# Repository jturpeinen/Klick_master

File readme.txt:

**********************************************************
*************  Important Instructions Follow  ************
**********************************************************

All files exported to: Z:\\47\\32\\4732651\\9\Eagle\2016-07-08_01-20-50\2016-07-08_01-20-50.xml

**********************************************************
*****************Schematic Instructions  *******************
**********************************************************

To import your new Schematic file into Eagle:

1. Unzip the downloaded folder files to local directory and Start Eagle.
2. Select "File"->"Open"->"Schematic..." from the menu at the top of
the screen.
3. Browse to your newly exported file and select the ".sch" file extension.
4. You should now see your schamtic available in Eagle.

**********************************************************
*******************  PCB Instructions  *******************
**********************************************************

To import your new BOARD file into Eagle:

1. Unzip the downloaded folder files to local directory and Start Eagle.
2. Select "File"->"Open"->"Board..." from the menu at the top of
the screen.
3. Browse to your newly exported file and select the ".brd" file extension.
4. Planes will need to be repoured to update the polygon fills
	1. Once your board is loaded and before the repour, the default design rule
	   should be updated for Mask and thermal relief.
		a. Goto Edit and select Design Rules.
			-Select Masks Tab; Set Stop (Min & Max) to 0.0mm
			-Select Supply Tab; Set Thermal Isolation to 0.0mm
	2. To pour the polygon fills, goto Tools and select Ratsnest
	3. The polygons should all be filled now.
5. You should now have an image of your board available in Eagle.

**********************************************************
*******************  LIB Instructions  *******************
**********************************************************

To import your new library into Eagle:

1. Start Eagle.
2. Select "File"->"New"->"Library" from the menu.
3. In the blank library window, select "File" -> "Execute Script"
from the menu.
5. Browse to your newly exported Eagle Script file (".scr" file extension)
6. After opening the file, the script will populate the new library.
Layer 93 should NOT exist.
7. Use "File"->"Save" (or "Save As..") to save the library to the desired
location in Eagle native format.

For additional information, please visit this site:
http://www.accelerated-designs.com/help/Eagle_import.html

You may also find this video helpful:
http://youtu.be/5jGuWY-Yy3Q

**********************************************************
**********************************************************
**********************************************************

Padstack "RX78p74Y236p22D0T" renamed to "RX78p74Y236p22D0"
Component "CC0805KRX7R9BB222" renamed to "CC0805KRX7R9BB222"
Component "GRM21BR61E475MA12L" renamed to "GRM21BR61E475MA12L"
Component "GRM31CR71H475KA12L" renamed to "GRM31CR71H475KA12L"
Component "TPS61170DRVR" renamed to "TPS61170DRVR"
Component "SRN6045-220M" renamed to "SRN6045-220M"
Component "CRCW040246K4FKED" renamed to "CRCW040246K4FKED"
Component "CRCW040210K5FKED" renamed to "CRCW040210K5FKED"
Component "CRCW0402226KFKED" renamed to "CRCW0402226KFKED"
Component "TP-1502" renamed to "TP-1502"
Component "PMEG6010CEH,115" renamed to "PMEG6010CEH,115"

Ultra Librarian Gold 8.1.44 Process Report

Message - Padstack "RX44Y57D0T" Shape(4) is a CIRCLE with no diameter.
Message - Padstack "RX44Y71D0T" Shape(4) is a CIRCLE with no diameter.
Message - Padstack "RX78p74Y236p22D0" Shape(4) is a CIRCLE with no diameter.
Message - Padstack "RX22Y24D0T" Shape(4) is a CIRCLE with no diameter.
Message - Padstack "RX24Y14D0T" Shape(4) is a CIRCLE with no diameter.
Message - Padstack "RX39Y63D0T" Shape(4) is a CIRCLE with no diameter.
Message - Padstack "R10470470000202A" Shape(4) is a CIRCLE with no diameter.
Message - Component "CC0805KRX7R9BB222" attribute "Cap" references text style "" that is not in the database.
The default pattern text style "H50s3" was substituted.
Message - Component "CC0805KRX7R9BB222" attribute "ESR" references text style "" that is not in the database.
The default pattern text style "H50s3" was substituted.
Message - Component "CC0805KRX7R9BB222" attribute "IRMS" references text style "" that is not in the database.
The default pattern text style "H50s3" was substituted.
Message - Component "CC0805KRX7R9BB222" attribute "VDC" references text style "" that is not in the database.
The default pattern text style "H50s3" was substituted.
Message - Component "GRM21BR61E475MA12L" attribute "Datasheet URL" references text style "" that is not in the database.
The default pattern text style "H50s3" was substituted.
Message - Component "GRM21BR61E475MA12L" attribute "Cap" references text style "" that is not in the database.
The default pattern text style "H50s3" was substituted.
Message - Component "GRM21BR61E475MA12L" attribute "ESR" references text style "" that is not in the database.
The default pattern text style "H50s3" was substituted.
Message - Component "GRM21BR61E475MA12L" attribute "IRMS" references text style "" that is not in the database.
The default pattern text style "H50s3" was substituted.
Message - Component "GRM21BR61E475MA12L" attribute "VDC" references text style "" that is not in the database.
The default pattern text style "H50s3" was substituted.
Message - Component "GRM31CR71H475KA12L" attribute "Cap" references text style "" that is not in the database.
The default pattern text style "H50s3" was substituted.
Message - Component "GRM31CR71H475KA12L" attribute "ESR" references text style "" that is not in the database.
The default pattern text style "H50s3" was substituted.
Message - Component "GRM31CR71H475KA12L" attribute "IRMS" references text style "" that is not in the database.
The default pattern text style "H50s3" was substituted.
Message - Component "GRM31CR71H475KA12L" attribute "VDC" references text style "" that is not in the database.
The default pattern text style "H50s3" was substituted.
Message - Component "TPS61170DRVR" attribute "Datasheet URL" references text style "" that is not in the database.
The default pattern text style "H50s3" was substituted.
Message - Component "TPS61170DRVR" attribute "Frequency" references text style "" that is not in the database.
The default pattern text style "H50s3" was substituted.
Message - Component "TPS61170DRVR" attribute "Imax" references text style "" that is not in the database.
The default pattern text style "H50s3" was substituted.
Message - Component "TPS61170DRVR" attribute "Package" references text style "" that is not in the database.
The default pattern text style "H50s3" was substituted.
Message - Component "TPS61170DRVR" attribute "Mktg_Package" references text style "" that is not in the database.
The default pattern text style "H50s3" was substituted.
Message - Component "TPS61170DRVR" attribute "NSID" references text style "" that is not in the database.
The default pattern text style "H50s3" was substituted.
Message - Component "SRN6045-220M" attribute "Datasheet URL" references text style "" that is not in the database.
The default pattern text style "H50s3" was substituted.
Message - Component "SRN6045-220M" attribute "L" references text style "" that is not in the database.
The default pattern text style "H50s3" was substituted.
Message - Component "SRN6045-220M" attribute "DCR" references text style "" that is not in the database.
The default pattern text style "H50s3" was substituted.
Message - Component "SRN6045-220M" attribute "IDC" references text style "" that is not in the database.
The default pattern text style "H50s3" was substituted.
Message - Component "CRCW040246K4FKED" attribute "Resistance" references text style "" that is not in the database.
The default pattern text style "H50s3" was substituted.
Message - Component "CRCW040246K4FKED" attribute "Power" references text style "" that is not in the database.
The default pattern text style "H50s3" was substituted.
Message - Component "CRCW040246K4FKED" attribute "Tolerance" references text style "" that is not in the database.
The default pattern text style "H50s3" was substituted.
Message - Component "CRCW040210K5FKED" attribute "Resistance" references text style "" that is not in the database.
The default pattern text style "H50s3" was substituted.
Message - Component "CRCW040210K5FKED" attribute "Power" references text style "" that is not in the database.
The default pattern text style "H50s3" was substituted.
Message - Component "CRCW040210K5FKED" attribute "Tolerance" references text style "" that is not in the database.
The default pattern text style "H50s3" was substituted.
Message - Component "CRCW0402226KFKED" attribute "Resistance" references text style "" that is not in the database.
The default pattern text style "H50s3" was substituted.
Message - Component "CRCW0402226KFKED" attribute "Power" references text style "" that is not in the database.
The default pattern text style "H50s3" was substituted.
Message - Component "CRCW0402226KFKED" attribute "Tolerance" references text style "" that is not in the database.
The default pattern text style "H50s3" was substituted.
Message - Component "PMEG6010CEH,115" attribute "Datasheet URL" references text style "" that is not in the database.
The default pattern text style "H50s3" was substituted.
Message - Component "PMEG6010CEH,115" attribute "Io" references text style "" that is not in the database.
The default pattern text style "H50s3" was substituted.
Message - Component "PMEG6010CEH,115" attribute "VRRM" references text style "" that is not in the database.
The default pattern text style "H50s3" was substituted.
Message - Component "PMEG6010CEH,115" attribute "VFatIo" references text style "" that is not in the database.
The default pattern text style "H50s3" was substituted.

TextStyle count:  25
Padstack count:   11
Pattern count:    7
Symbol count:     6
Component count:  10

Export

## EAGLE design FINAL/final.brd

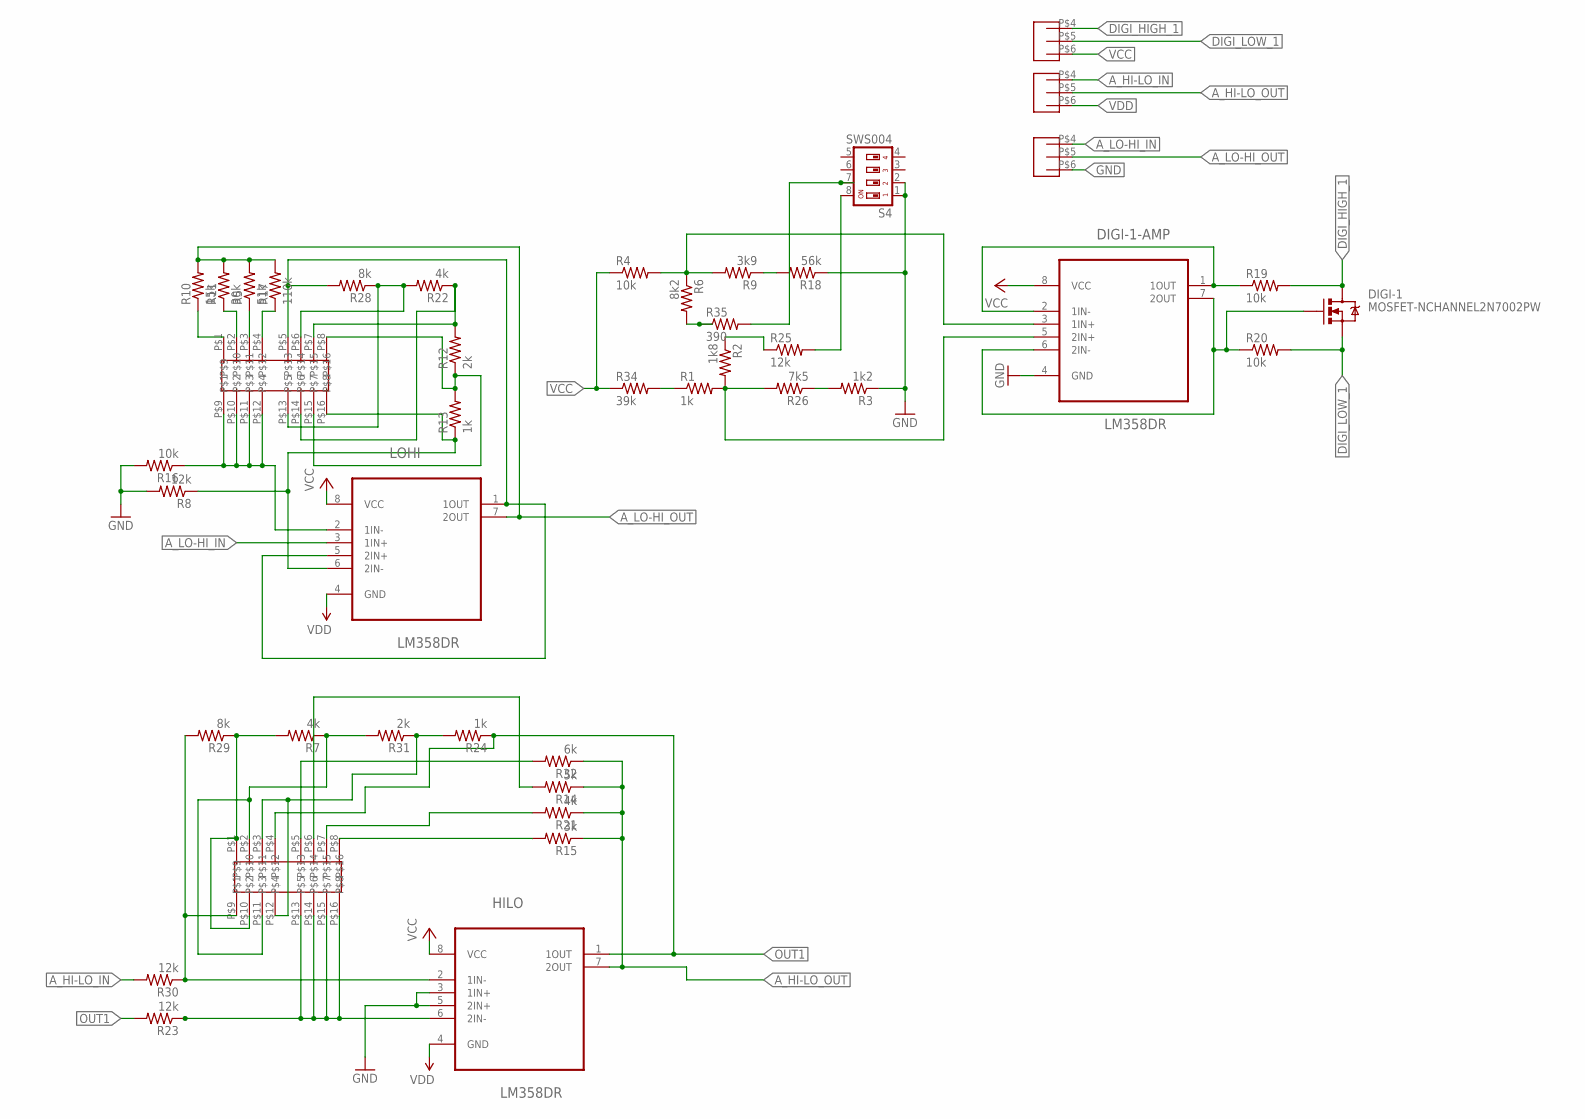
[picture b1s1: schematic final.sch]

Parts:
DIGI-1: MOSFET-NCHANNEL2N7002PW; SOT323
DIGI-1-AMP: LM358DR; SOIC127P600X175-8N
HILO: LM358DR; SOIC127P600X175-8N
LOHI: LM358DR; SOIC127P600X175-8N
R1, R13: 1k; R0805
R2: 1k8; R0805
R3: 1k2; R0805
R4, R16, R19, R20: 10k; R0805
R5: 51k; R0805
R6: 8k2; R0805
R7, R22: 4k; 0207/15
R8, R23, R25, R30: 12k; R0805
R9: 3k9; R0805
R10: 15k; R0805
R11: 30k; R0805
R12, R31: 2k; 0207/15
R14: 5k; R0805
R15: 3k; R0805
R17: 110k; R0805
R18: 56k; R0805
R21: 4k; R0805
R24: 1k; 0207/15
R26: 7k5; R0805
R28: 8k; 0207/15
R29: 8k; R0805
R32: 6k; R0805
R34: 39k; R0805
R35: 390; R0805
S4: SWS004; SMS-004
U$2, U$3: USCO_8PIN_SWITCH
U$4, U$5, U$6: 5.08PITCHTERMINAL; 10KPL508

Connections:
A_HI-LO_IN: R30.2, U$4.P$4
A_HI-LO_OUT: HILO.7 (2OUT), R14.1, R15.1, R21.1, R32.1, U$4.P$5
A_LO-HI_IN: LOHI.3 (1IN+), U$6.P$4
A_LO-HI_OUT: LOHI.7 (2OUT), R5.2, R10.2, R11.2, R17.2, U$6.P$5
DI-1: DIGI-1-AMP.1 (1OUT), DIGI-1-AMP.2 (1IN-), R19.1
DIGI_HIGH_1: DIGI-1.3 (D), R19.2, U$5.P$4
DIGI_LOW_1: DIGI-1.2 (S), R20.2, U$5.P$5
GND: DIGI-1-AMP.4 (GND), HILO.3 (1IN+), HILO.5 (2IN+), R3.1, R8.2, R16.2, R18.1, S4.1, S4.2, U$6.P$6
unnamed: DIGI-1-AMP.3 (1IN+), R4.2, R6.1, R9.2
unnamed: R25.2, S4.8
unnamed: R6.2, R35.1
unnamed: DIGI-1-AMP.5 (2IN+), R1.2, R2.2, R26.2
unnamed: DIGI-1.1 (G), DIGI-1-AMP.6 (2IN-), DIGI-1-AMP.7 (2OUT), R20.1
unnamed: R9.1, R18.2
unnamed: HILO.2 (1IN-), R29.2, R30.1, U$2.P$9
unnamed: R2.1, R25.1
unnamed: R10.1, U$3.P$1
unnamed: R11.1, U$3.P$2
unnamed: R1.1, R34.2
unnamed: R5.1, U$3.P$3
unnamed: R17.1, U$3.P$4
unnamed: LOHI.1 (1OUT), LOHI.5 (2IN+), R28.2, U$3.P$5
unnamed: R7.2, R29.1, U$2.P$1, U$2.P$10
unnamed: R22.2, R28.1, U$3.P$6, U$3.P$13
unnamed: R12.2, R22.1, U$3.P$7, U$3.P$14
unnamed: R7.1, R31.2, U$2.P$2, U$2.P$11
unnamed: R24.2, R31.1, U$2.P$3, U$2.P$12
unnamed: R15.2, U$2.P$8
unnamed: R21.2, U$2.P$7
unnamed: R14.2, U$2.P$6
unnamed: R32.2, U$2.P$5
unnamed: R3.2, R26.1
unnamed: HILO.6 (2IN-), R23.1, U$2.P$13, U$2.P$14, U$2.P$15, U$2.P$16
unnamed: R12.1, R13.2, U$3.P$8, U$3.P$15
unnamed: R35.2, S4.7
unnamed: LOHI.2 (1IN-), R16.1, U$3.P$9, U$3.P$10, U$3.P$11, U$3.P$12
unnamed: LOHI.6 (2IN-), R8.1, R13.1, U$3.P$16
OUT1: HILO.1 (1OUT), R23.2, R24.1, U$2.P$4
VCC: DIGI-1-AMP.8 (VCC), HILO.8 (VCC), LOHI.8 (VCC), R4.1, R34.1, U$5.P$6
VDD: HILO.4 (GND), LOHI.4 (GND), U$4.P$6

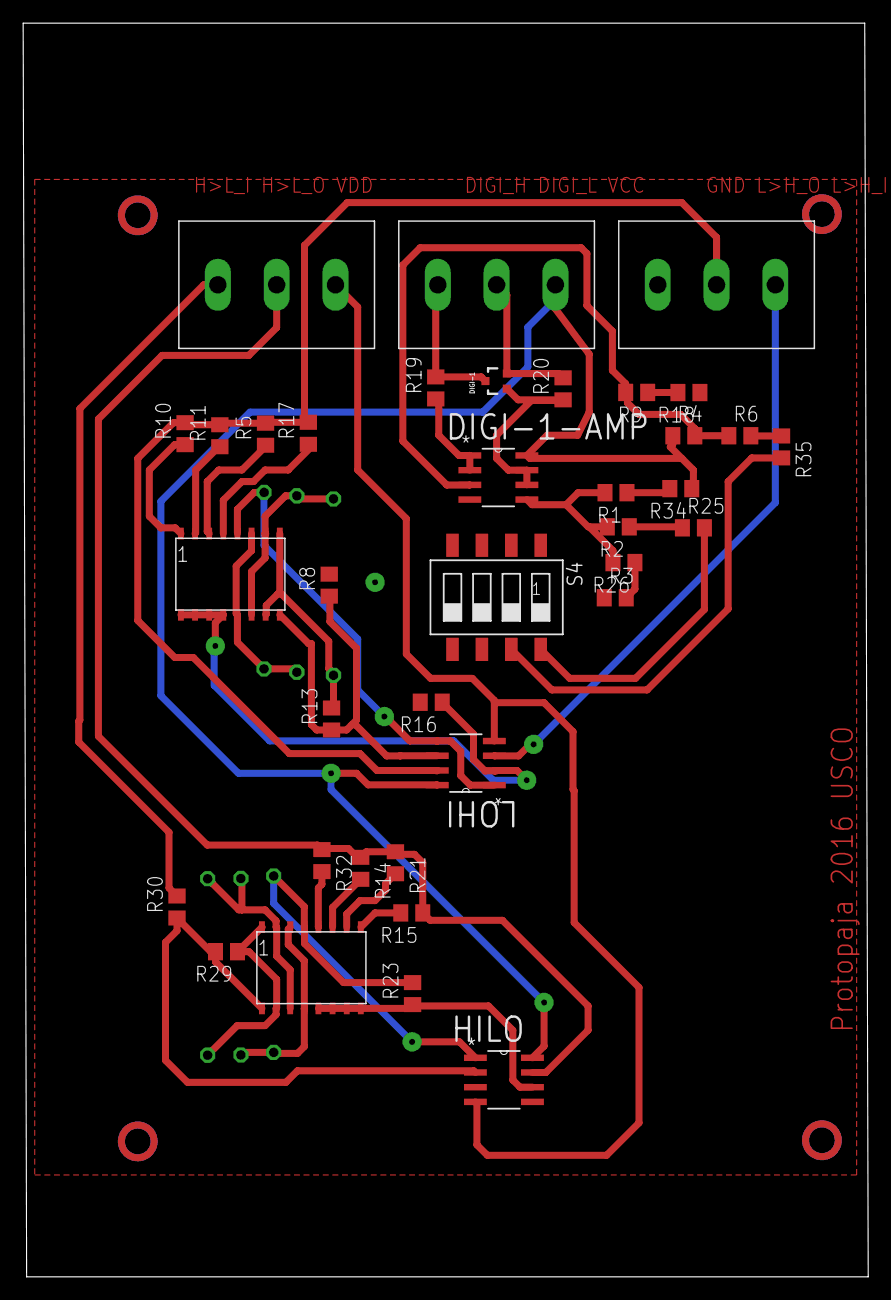
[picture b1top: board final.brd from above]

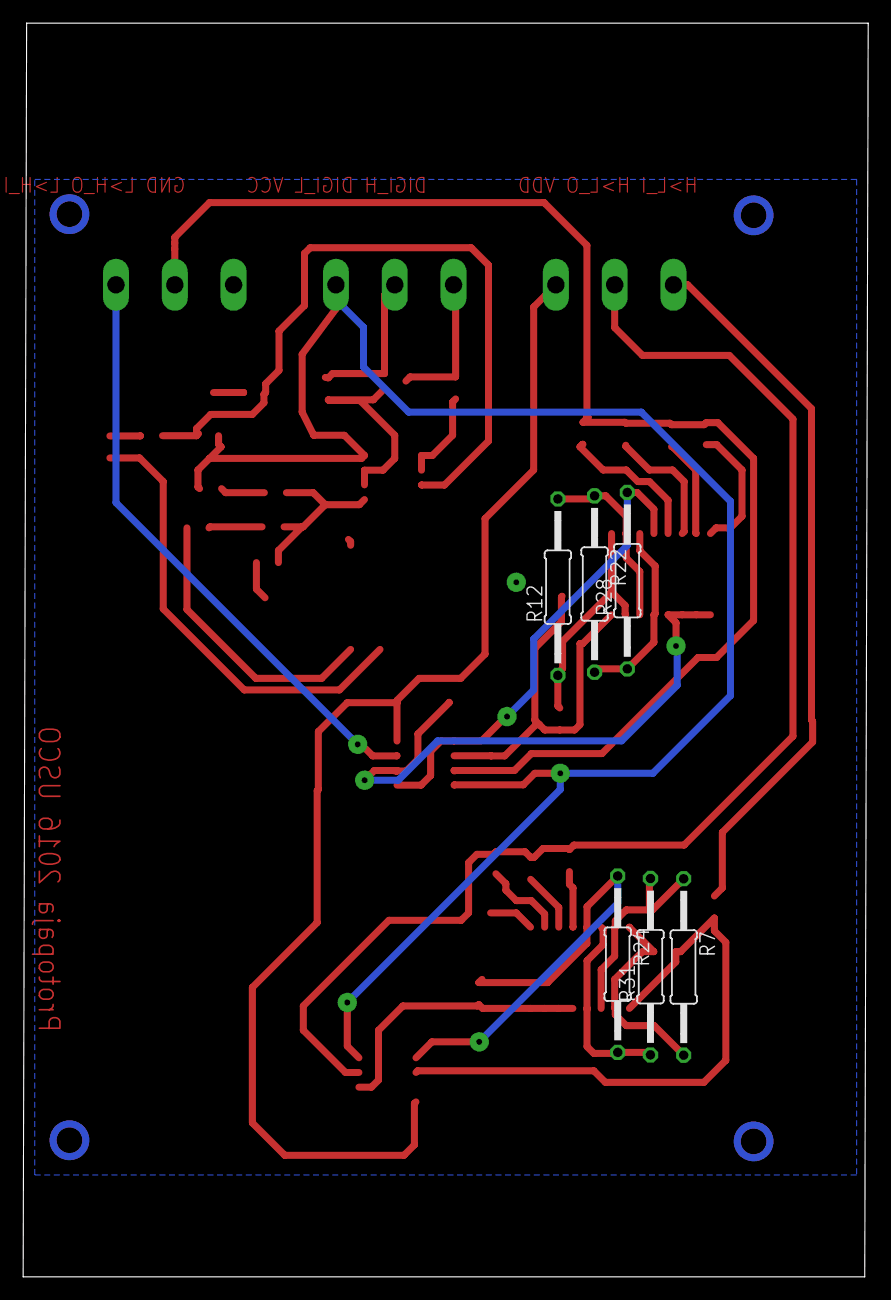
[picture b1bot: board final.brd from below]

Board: 2 copper layers, 73.0 x 108.3 mm, 43 parts (6 on the bottom side), 40 nets.

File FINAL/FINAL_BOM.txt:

Partlist exported from C:/Users/PAJA/Documents/eagle/Uadi-voleco/Klick_master/Greippi/Greippi.sch at 6.8.2016 21:23

Qty Value                   Device                  Package            Parts                  Description               MPN     OC_FARNELL OC_NEWARK PACKAGE PROD_ID     SUPPLIER         
4   10k                     R-US_R0805              R0805              R4, R16, R19, R20      RESISTOR, American symbol                                                                   
1   110k                    R-US_R0805              R0805              R17                    RESISTOR, American symbol                                                                   
4   12k                     R-US_R0805              R0805              R8, R23, R25, R30      RESISTOR, American symbol                                                                   
1   15k                     R-US_R0805              R0805              R10                    RESISTOR, American symbol                                                                   
1   1k                      R-US_0207/15            0207/15            R24                    RESISTOR, American symbol                                                                   
2   1k                      R-US_R0805              R0805              R1, R13                RESISTOR, American symbol                                                                   
1   1k2                     R-US_R0805              R0805              R3                     RESISTOR, American symbol                                                                   
1   1k8                     R-US_R0805              R0805              R2                     RESISTOR, American symbol                                                                   
2   2k                      R-US_0207/15            0207/15            R12, R31               RESISTOR, American symbol                                                                   
1   30k                     R-US_R0805              R0805              R11                    RESISTOR, American symbol                                                                   
1   390                     R-US_R0805              R0805              R35                    RESISTOR, American symbol                                                                   
1   39k                     R-US_R0805              R0805              R34                    RESISTOR, American symbol                                                                   
1   3k                      R-US_R0805              R0805              R15                    RESISTOR, American symbol                                                                   
1   3k9                     R-US_R0805              R0805              R9                     RESISTOR, American symbol                                                                   
2   4k                      R-US_0207/15            0207/15            R7, R22                RESISTOR, American symbol                                                                   
1   4k                      R-US_R0805              R0805              R21                    RESISTOR, American symbol                                                                   
3   5.08PITCHTERMINAL       5.08PITCHTERMINAL       10KPL508           U$4, U$5, U$6                                                                                                      
1   51k                     R-US_R0805              R0805              R5                     RESISTOR, American symbol                                                                   
1   56k                     R-US_R0805              R0805              R18                    RESISTOR, American symbol                                                                   
1   5k                      R-US_R0805              R0805              R14                    RESISTOR, American symbol                                                                   
1   6k                      R-US_R0805              R0805              R32                    RESISTOR, American symbol                                                                   
1   7k5                     R-US_R0805              R0805              R26                    RESISTOR, American symbol                                                                   
1   8k                      R-US_0207/15            0207/15            R28                    RESISTOR, American symbol                                                                   
1   8k                      R-US_R0805              R0805              R29                    RESISTOR, American symbol                                                                   
1   8k2                     R-US_R0805              R0805              R6                     RESISTOR, American symbol                                                                   
3   LM358DR                 LM358DR                 SOIC127P600X175-8N DIGI-1-AMP, HILO, LOHI OPERATIONAL AMPLIFIERS    LM358DR 1831865    34K7599   SOIC-8              Texas Instruments
1   MOSFET-NCHANNEL2N7002PW MOSFET-NCHANNEL2N7002PW SOT323             DIGI-1                 Common NMOSFET Parts                                           TRANS-11151                  
1   SWS004                  SWS004                  SMS-004            S4                     SMD Dip Switch 4 pol.                                                                       
2   USCO_8PIN_SWITCH        USCO_8PIN_SWITCH        USCO_8PIN_SWITCH   U$2, U$3

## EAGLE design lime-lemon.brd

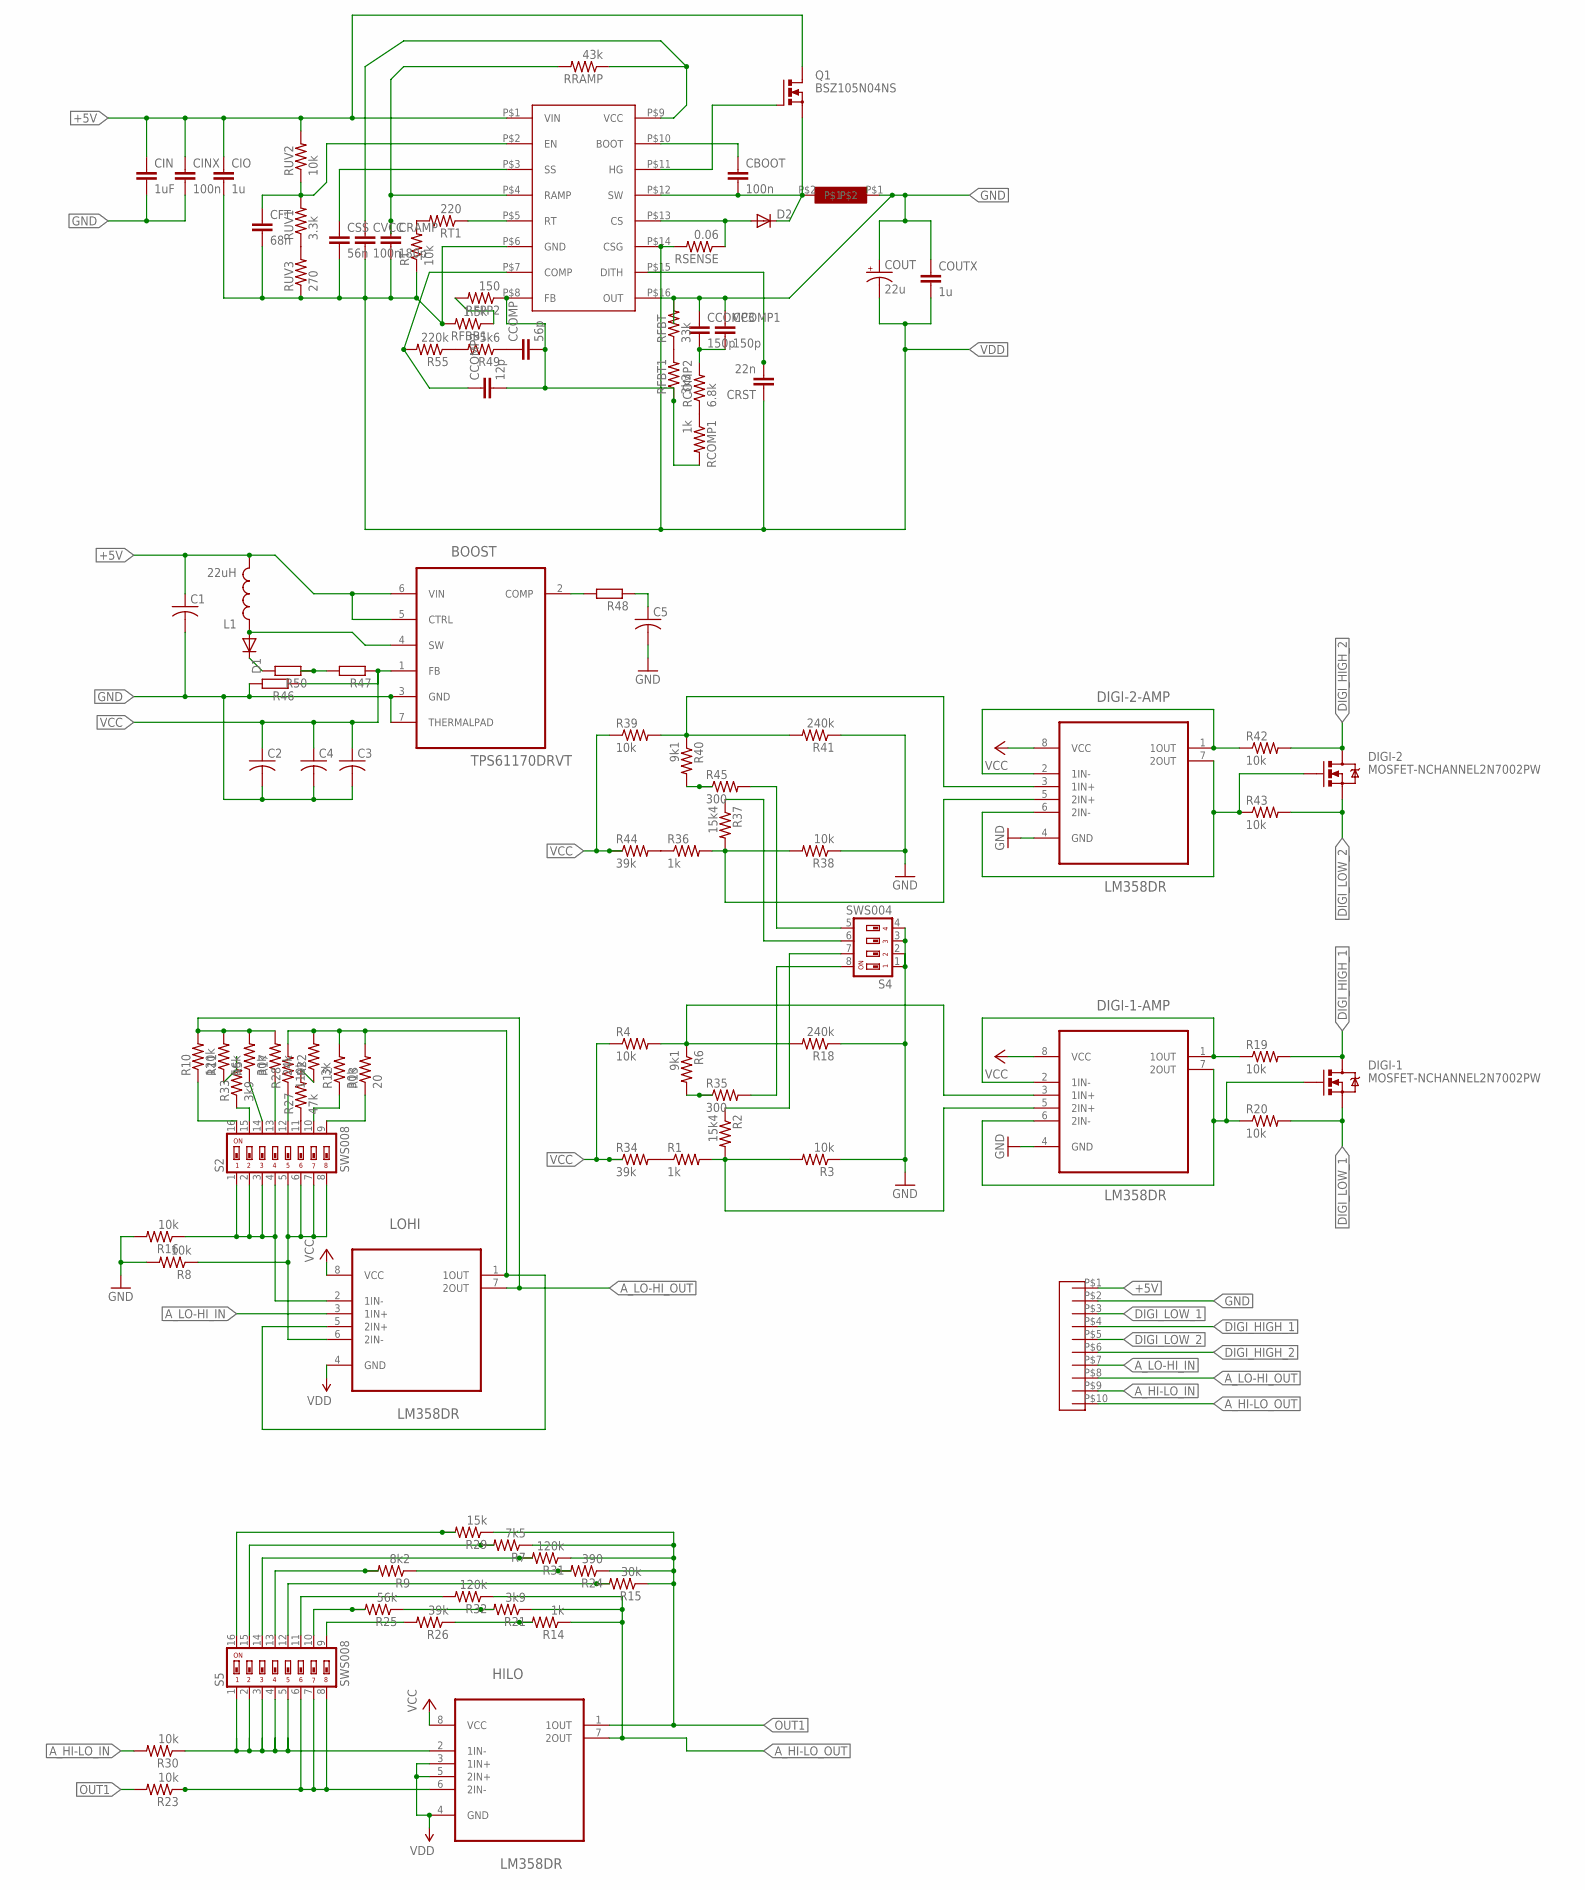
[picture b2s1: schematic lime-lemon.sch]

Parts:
BOOST: TPS61170DRVT; SON65P210X210X80-7N
C1, C3, C4, C5: C-USC1206; C1206
C2: C-USC0805; C0805
CBOOT: 100n; C0805
CCOMP: 56p; C0805
CCOMP1, CCOMP3: 150p; C0805
CCOMP2: 12p; C0805
CFT: 68n; C0805
CIN: 1uF; C0805
CINX: 100n; C0805
CIO: 1u; C0805
COUT: 22u; E5-5
COUTX: 1u; C0805
CRAMP: 180p; C0805
CRST: 22n; C0805
CSS: 56n; C0805
CVCC: 100n; C0805
D1, D2: DIODE-SOD123; SOD123
DIGI-1, DIGI-2: MOSFET-NCHANNEL2N7002PW; SOT323
DIGI-1-AMP, DIGI-2-AMP: LM358DR; SOIC127P600X175-8N
HILO: LM358DR; SOIC127P600X175-8N
L1: 22uH; SRN6045
LOHI: LM358DR; SOIC127P600X175-8N
Q1: BSZ105N04NS; PG-TDSON-8
R1, R14, R36: 1k; R0805
R2, R37: 15k4; R0805
R3, R4, R8, R16, R19, R20, R23, R30, R38, R39, R42, R43: 10k; R0805
R5, R12, R15: 30k; R0805
R6, R40: 9k1; R0805
R7: 7k5; R0805
R9: 8k2; R0805
R10, R31, R32: 120k; R0805
R11, R25: 56k; R0805
R13: 20; R0805
R17: 24k; R0805
R18, R41: 240k; R0805
R21, R33: 3k9; R0805
R22: 3k; R0805
R24: 390; R0805
R26, R34, R44: 39k; R0805
R27: 47k; R0805
R28: 110k; R0805
R29: 15k; R0805
R35, R45: 300; R0805
R46, R47, R48, R50: R-EU_R0805; R0805
R49: 5k6; R0805
R55: 220k; R0805
RCOMP1: 1k; R0805
RCOMP2: 6.8k; R0805
RFBB1: 1.5k; R0805
RFBT: 33k; R0805
RFBT1: 3k3; R0805
RFPP2: 150; R0805
RRAMP: 43k; R0805
RSENSE: 0.06; R0805
RT: 10k; R0805
RT1: 220; R0805
RUV1: 3.3k; R0805
RUV2: 10k; R0805
RUV3: 270; R0805
S2, S5: SWS008; SMS-008
S4: SWS004; SMS-004
U$1: 5.08PITCHTERMINAL; 10KPL508
U$2: LM5088
U$3: KLICK_INDUCTOR01

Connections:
+5V: BOOST.5 (CTRL), BOOST.6 (VIN), C1.1, CIN.1, CINX.1, CIO.1, L1.2, Q1.5 (D), Q1.6 (D), Q1.7 (D), Q1.8 (D), Q1.TH (D), RUV2.2, U$1.P$1, U$2.P$1 (VIN)
A_HI-LO_IN: R30.2, U$1.P$9
A_HI-LO_OUT: HILO.7 (2OUT), R14.1, R21.1, R32.1, U$1.P$10
A_LO-HI_IN: LOHI.3 (1IN+), U$1.P$7
A_LO-HI_OUT: LOHI.7 (2OUT), R5.2, R10.2, R11.2, R17.2, U$1.P$8
DI-1: DIGI-1-AMP.1 (1OUT), DIGI-1-AMP.2 (1IN-), R19.1
DIGI_HIGH_1: DIGI-1.3 (D), R19.2, U$1.P$4
DIGI_HIGH_2: DIGI-2.3 (D), R42.2, U$1.P$6
DIGI_LOW_1: DIGI-1.2 (S), R20.2, U$1.P$3
DIGI_LOW_2: DIGI-2.2 (S), R43.2, U$1.P$5
GND: BOOST.3 (GND), BOOST.7 (THERMALPAD), C1.2, C2.2, C3.2, C4.2, C5.2, CCOMP1.1, CCOMP3.1, CIN.2, CINX.2, COUT.+, COUTX.1, DIGI-1-AMP.4 (GND), DIGI-2-AMP.4 (GND), R3.1, R8.2, R16.2, R18.1, R38.1, R41.1, R46.2, RFBT.2, S4.1, S4.2, S4.3, S4.4, U$1.P$2, U$2.P$16 (OUT), U$3.P$1
unnamed: DIGI-1-AMP.3 (1IN+), R4.2, R6.1, R18.2
unnamed: R2.1, S4.7
unnamed: R6.2, R35.1
unnamed: DIGI-1-AMP.5 (2IN+), R1.2, R2.2, R3.2
unnamed: DIGI-1.1 (G), DIGI-1-AMP.6 (2IN-), DIGI-1-AMP.7 (2OUT), R20.1
unnamed: DIGI-2-AMP.5 (2IN+), R36.2, R37.2, R38.2
unnamed: HILO.2 (1IN-), R30.1, S5.1, S5.2, S5.3, S5.4, S5.5
unnamed: DIGI-2-AMP.3 (1IN+), R39.2, R40.1, R41.2
unnamed: R10.1, S2.16
unnamed: R33.1, S2.15
unnamed: R1.1, R34.2
unnamed: R5.1, S2.14
unnamed: R17.1, S2.13
unnamed: R28.1, S2.12
unnamed: R27.1, S2.11
unnamed: R12.1, S2.10
unnamed: R13.1, S2.9
unnamed: R29.2, S5.16
unnamed: LOHI.1 (1OUT), LOHI.5 (2IN+), R12.2, R13.2, R22.2, R28.2
unnamed: R7.2, S5.15
unnamed: R31.2, S5.14
unnamed: R9.2, S5.13
unnamed: R15.2, S5.12
unnamed: R32.2, S5.11
unnamed: HILO.6 (2IN-), R23.1, S5.6, S5.7, S5.8
unnamed: R25.2, S5.10
unnamed: R26.2, S5.9
unnamed: R14.2, R26.1
unnamed: R21.2, R25.1
unnamed: R9.1, R24.2
unnamed: R22.1, R27.2
unnamed: R11.1, R33.2
unnamed: R35.2, S4.8
unnamed: CFT.1, RUV1.2, RUV2.1, U$2.P$2 (EN)
unnamed: BOOST.4 (SW), D1.A, L1.1
unnamed: CSS.1, U$2.P$3 (SS)
unnamed: LOHI.2 (1IN-), R16.1, S2.1, S2.2, S2.3, S2.4
unnamed: R47.2, R50.1
unnamed: CVCC.1, RRAMP.1, U$2.P$9 (VCC)
unnamed: BOOST.2 (COMP), R48.2
unnamed: LOHI.6 (2IN-), R8.1, S2.5, S2.6, S2.7, S2.8
unnamed: C5.1, R48.1
unnamed: D2.A, RSENSE.1, U$2.P$13 (CS)
unnamed: CRAMP.1, RRAMP.2, U$2.P$4 (RAMP)
unnamed: RT.2, RT1.2
unnamed: RUV1.1, RUV3.2
unnamed: CCOMP.1, R49.1
unnamed: CCOMP.2, CCOMP2.2, RCOMP1.2, RFBT1.1, RFPP2.1, U$2.P$8 (FB)
unnamed: CCOMP2.1, R55.2, U$2.P$7 (COMP)
unnamed: CBOOT.1, U$2.P$10 (BOOT)
unnamed: CRST.2, U$2.P$15 (DITH)
unnamed: CBOOT.2, D2.C, Q1.1 (S), Q1.2 (S), Q1.3 (S), U$2.P$12 (SW), U$3.P$2
unnamed: RFBB1.1, RFPP2.2
unnamed: DIGI-2-AMP.1 (1OUT), DIGI-2-AMP.2 (1IN-), R42.1
unnamed: DIGI-2.1 (G), DIGI-2-AMP.6 (2IN-), DIGI-2-AMP.7 (2OUT), R43.1
unnamed: Q1.4 (G), U$2.P$11 (HG)
unnamed: R49.2, R55.1
unnamed: R37.1, S4.6
unnamed: R36.1, R44.2
unnamed: R40.2, R45.1
unnamed: R45.2, S4.5
unnamed: CCOMP1.2, CCOMP3.2, RCOMP2.2
unnamed: RT1.1, U$2.P$5 (RT)
unnamed: RCOMP1.1, RCOMP2.1
unnamed: RFBT.1, RFBT1.2
unnamed: D1.C, R50.2
OUT1: HILO.1 (1OUT), R7.1, R15.1, R23.2, R24.1, R29.1, R31.1
VCC: BOOST.1 (FB), C2.1, C3.1, C4.1, DIGI-1-AMP.8 (VCC), DIGI-2-AMP.8 (VCC), HILO.8 (VCC), LOHI.8 (VCC), R4.1, R34.1, R39.1, R44.1, R46.1, R47.1
VDD: CFT.2, CIO.2, COUT.-, COUTX.2, CRAMP.2, CRST.1, CSS.2, CVCC.2, HILO.3 (1IN+), HILO.4 (GND), HILO.5 (2IN+), LOHI.4 (GND), RFBB1.2, RSENSE.2, RT.1, RUV3.1, U$2.P$6 (GND), U$2.P$14 (CSG)

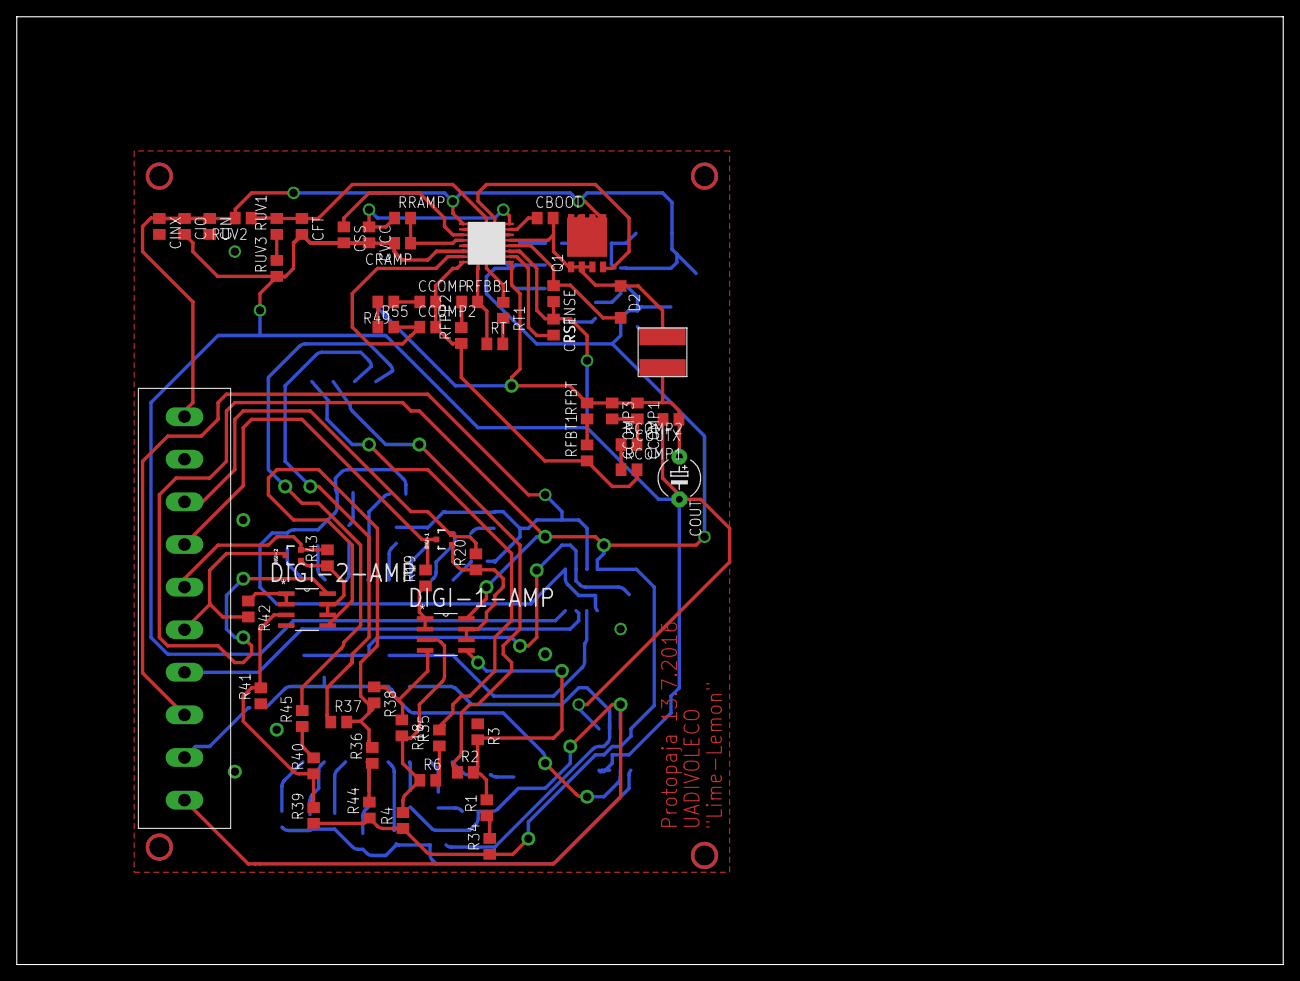
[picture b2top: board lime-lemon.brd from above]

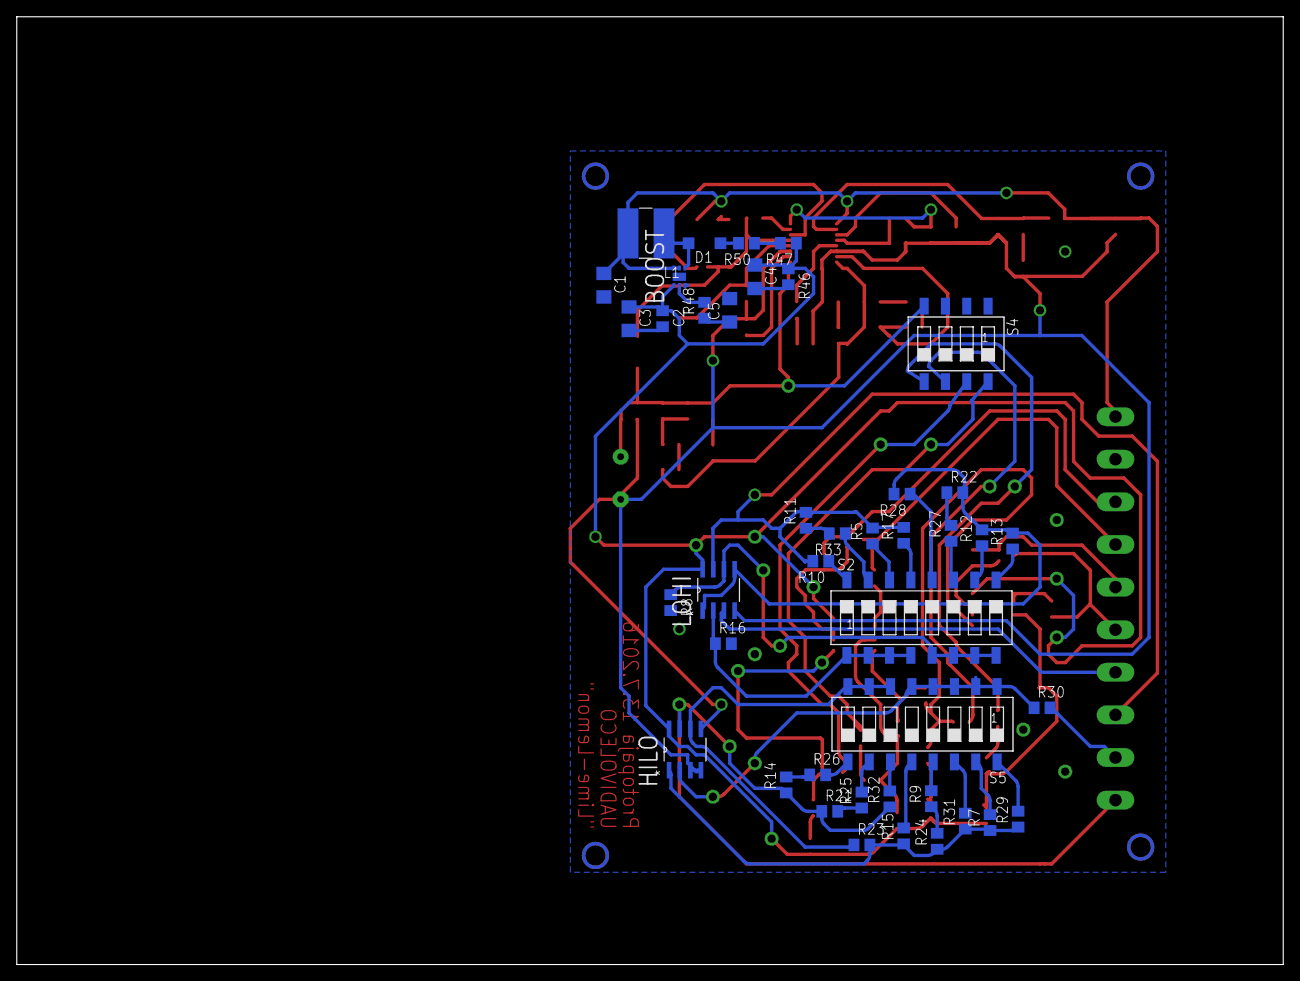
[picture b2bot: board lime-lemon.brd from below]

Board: 2 copper layers, 151.0 x 113.0 mm, 101 parts (42 on the bottom side), 80 nets.

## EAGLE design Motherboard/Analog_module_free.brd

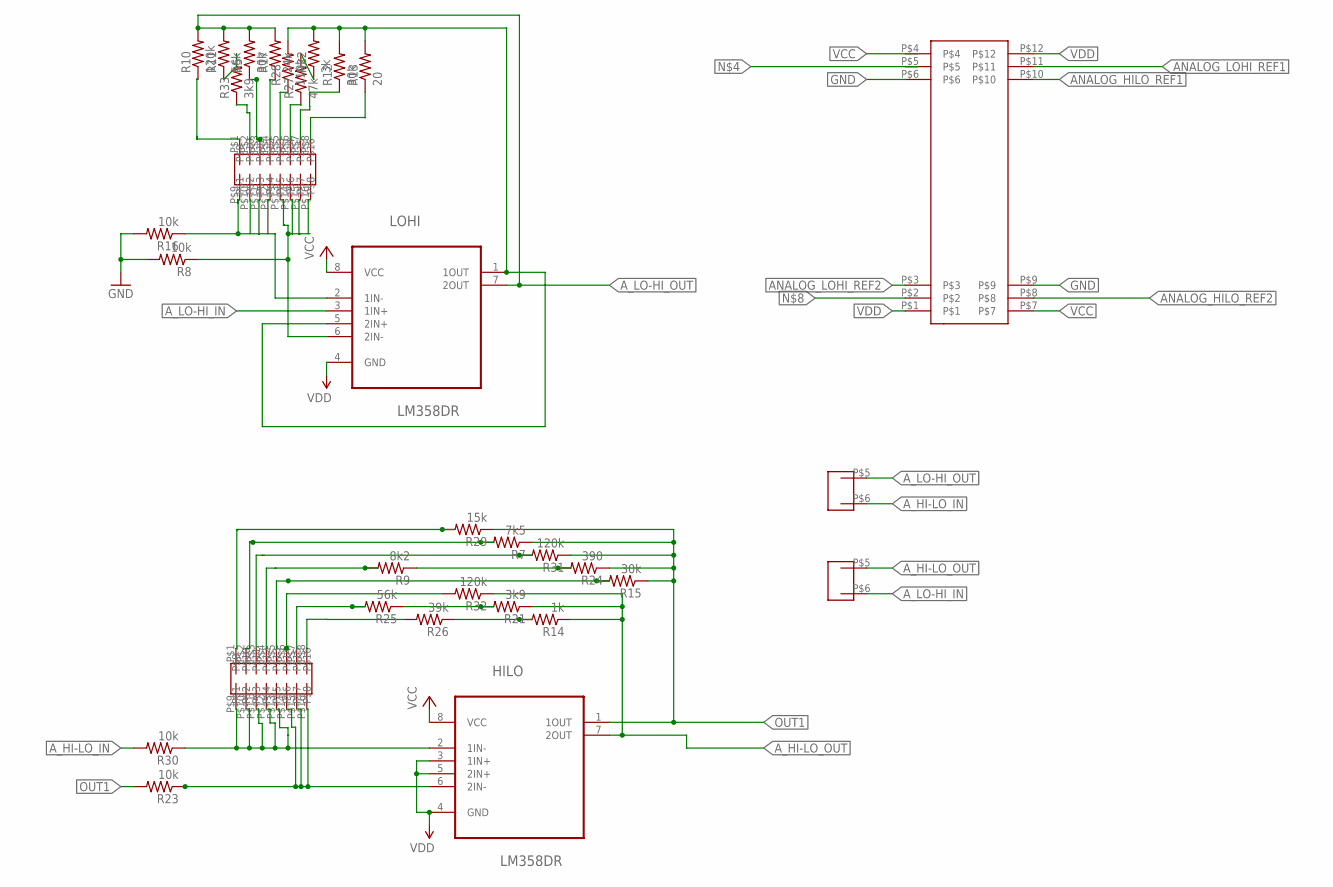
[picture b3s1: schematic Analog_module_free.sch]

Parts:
HILO: LM358DR; SOIC127P600X175-8N
LOHI: LM358DR; SOIC127P600X175-8N
R5, R12, R15: 30k; R0805
R7: 7k5; R0805
R8, R16, R23, R30: 10k; R0805
R9: 8k2; R0805
R10, R31, R32: 120k; R0805
R11, R25: 56k; R0805
R13: 20; R0805
R14: 1k; R0805
R17: 24k; R0805
R21, R33: 3k9; R0805
R22: 3k; R0805
R24: 390; R0805
R26: 39k; R0805
R27: 47k; R0805
R28: 110k; R0805
R29: 15k; R0805
U$1: MODULE_CONNECTOR
U$2, U$3: 5.08PITCHTERMINAL; 10KPL508
U$4, U$5: USCO_8PIN_SWITCH

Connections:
ANALOG_HILO_REF1: U$1.P$10
ANALOG_HILO_REF2: U$1.P$8
ANALOG_LOHI_REF1: U$1.P$11
ANALOG_LOHI_REF2: U$1.P$3
A_HI-LO_IN: R30.2, U$2.P$6
A_HI-LO_OUT: HILO.7 (2OUT), R14.1, R21.1, R32.1, U$3.P$5
A_LO-HI_IN: LOHI.3 (1IN+), U$3.P$6
A_LO-HI_OUT: LOHI.7 (2OUT), R5.2, R10.2, R11.2, R17.2, U$2.P$5
GND: R8.2, R16.2, U$1.P$6, U$1.P$9
unnamed: HILO.2 (1IN-), R30.1
unnamed: LOHI.1 (1OUT), LOHI.5 (2IN+), R12.2, R13.2, R22.2, R28.2
unnamed: R31.2, U$5.P$3
unnamed: R32.2, U$5.P$6
unnamed: HILO.6 (2IN-), R23.1
unnamed: R14.2, R26.1
unnamed: R21.2, R25.1
unnamed: R9.1, R24.2
unnamed: R22.1, R27.2
unnamed: R11.1, R33.2
unnamed: LOHI.2 (1IN-), R16.1
unnamed: LOHI.6 (2IN-), R8.1
OUT1: HILO.1 (1OUT), R7.1, R15.1, R23.2, R24.1, R29.1, R31.1
VCC: HILO.8 (VCC), LOHI.8 (VCC), U$1.P$7
VDD: HILO.3 (1IN+), HILO.4 (GND), HILO.5 (2IN+), LOHI.4 (GND), U$1.P$1, U$1.P$12

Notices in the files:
parts and their libraries:
SparkFun-DiscreteSemi: Licensing: Creative Commons ShareAlike 4.0 International - https://creativecommons.org/licenses/by-sa/4.0
